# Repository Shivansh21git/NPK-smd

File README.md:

# 🌱 Bhoomitra (Krishi Sarthi) – Smart NPK Soil Monitoring System

## 📌 Overview

**Bhoomitra (Krishi Sarthi)** is an embedded + IoT-based smart agriculture system designed to monitor **soil nutrient levels (NPK)** and assist farmers in making data-driven fertilization decisions.

The latest version introduces a **compact, optimized hardware architecture**, making the system more portable, robust, and suitable for real-world deployment in farms.

---

## 🎯 Problem Statement

Farmers often apply fertilizers based on guesswork, which leads to:

* Overuse of chemicals
* Increased cost
* Soil degradation
* Reduced crop yield

**Bhoomitra solves this by providing real-time soil nutrient insights.**

---

## 🧠 System Architecture

### 🔷 High-Level Architecture

```
Soil → NPK Sensor → Microcontroller → Data Processing → Output (Display / IoT)
```

### 🔷 Functional Blocks

1. **Sensing Layer**

   * NPK sensor measures Nitrogen, Phosphorus, Potassium
2. **Processing Layer**

   * Microcontroller processes raw sensor data
3. **Communication Layer (optional)**

   * Sends data to cloud / mobile app (if IoT enabled)
4. **Output Layer**

   * Displays readings or recommendations

---

## 🔌 Hardware Architecture

### 🧩 Components Used

* NPK Soil Sensor
* Microcontroller (Arduino / ESP32 / similar)
* Power Supply Module
* Display (LCD/OLED) or Serial Output
* Communication Module (WiFi / GSM – optional)

### ⚙️ Hardware Design Improvements

* ✅ Compact PCB / module layout
* ✅ Reduced wiring complexity
* ✅ Lower power consumption
* ✅ Field-ready enclosure design
* ✅ Improved durability for outdoor usage

### 🔄 Data Flow (Hardware)

1. Sensor probes inserted into soil
2. Sensor outputs analog/digital signals
3. Microcontroller reads signals via ADC/UART
4. Data is processed and calibrated
5. Output is displayed or transmitted

---

## 💻 Software Architecture

### 🧱 Software Layers

#### 1. Sensor Interface Layer

* Handles communication with NPK sensor
* Reads raw values (via UART / Analog pins)

#### 2. Data Processing Layer

* Calibration of sensor values
* Conversion into usable NPK units
* Filtering noise (basic smoothing if applied)

#### 3. Logic Layer

* Determines soil fertility status
* Can map values to:

  * Low / Medium / High nutrient levels
* Optional: fertilizer recommendation logic

#### 4. Output Layer

* Serial Monitor / LCD display
* IoT dashboard (if connected)

---

## 🔄 Working Principle

1. The NPK sensor is inserted into soil.
2. It measures nutrient concentration levels.
3. Microcontroller reads and processes the data.
4. Values are converted into meaningful units.
5. Output is shown to the user or transmitted.
6. Farmer uses insights for fertilizer planning.

---

## 🌐 IoT Integration (Optional)

* Real-time monitoring via cloud
* Data logging for analysis
* Remote farm monitoring
* Mobile-based access

---

## 📊 Example Use Case

* Farmer checks soil before sowing
* Detects low nitrogen level
* Applies only required fertilizer
* Saves cost and improves yield

---

## 🚀 Advantages

* 🌱 Promotes precision agriculture
* 💰 Reduces fertilizer waste
* 📈 Improves crop productivity
* 📦 Compact and portable design
* 🔧 Easy to deploy and maintain

---

## 🔮 Future Enhancements

* AI-based fertilizer recommendation
* Mobile app integration
* GPS-based soil mapping
* Multi-parameter sensing (pH, moisture, temperature)

---

## 📂 Repository Contents

* Embedded code
* Circuit design / hardware files
* Documentation

---

## 👨‍💻 Author

Shivansh
**Project:** Bhoomitra (Krishi Sarthi)

---

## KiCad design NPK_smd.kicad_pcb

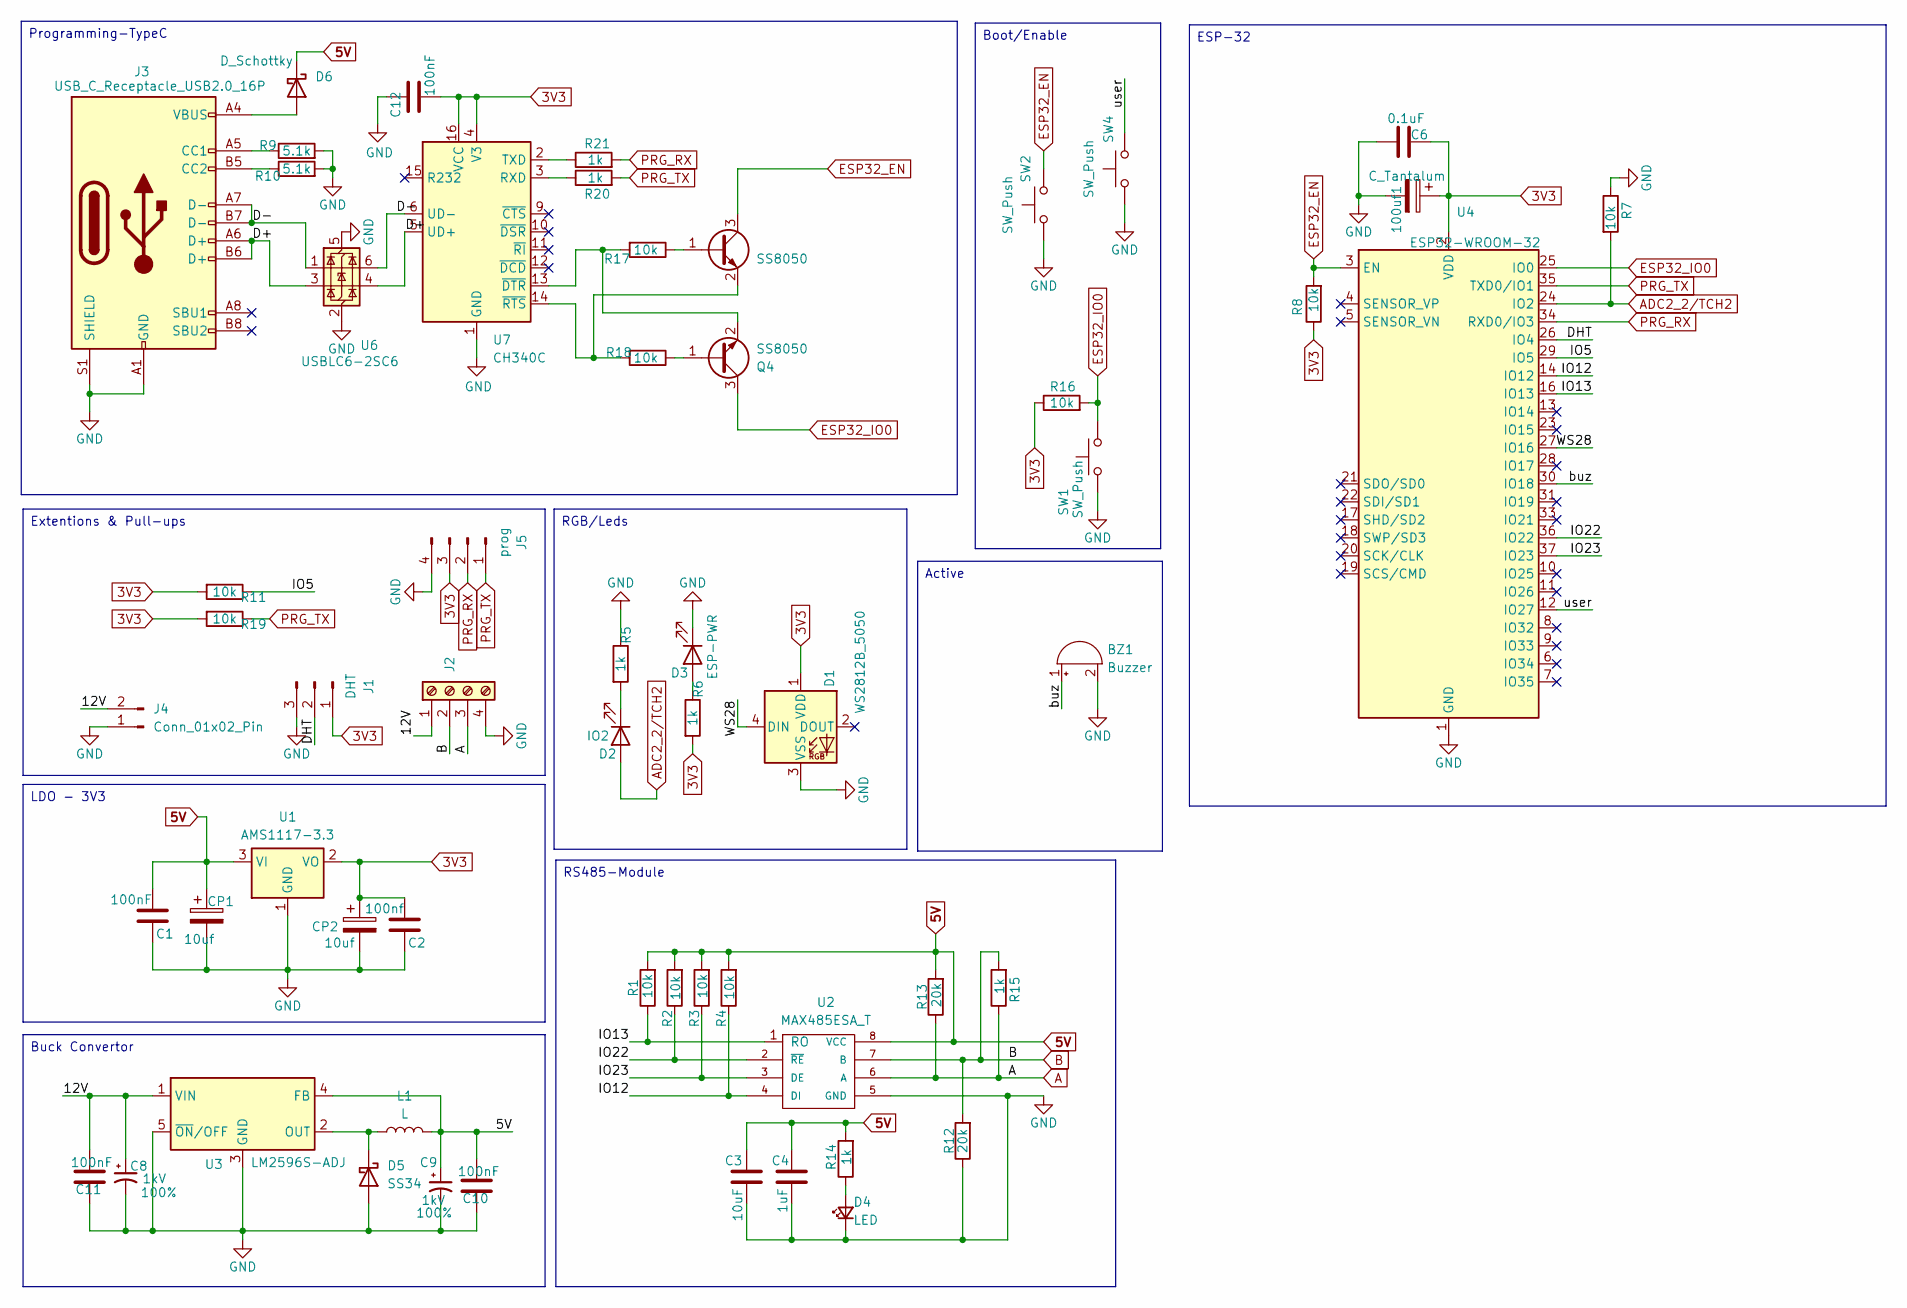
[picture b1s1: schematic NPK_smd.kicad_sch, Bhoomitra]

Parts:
100uf1: C_Tantalum; CP_EIA-3216-10_Kemet-I
BZ1: Buzzer; Buzzer_12x9.5RM7.6
C1, C10, C11, C12: 100nF; C_1206_3216Metric_Pad1.33x1.80mm_HandSolder
C2: 100nf; C_1206_3216Metric_Pad1.33x1.80mm_HandSolder
C3: 10uF; C_1206_3216Metric_Pad1.33x1.80mm_HandSolder
C4: 1uF; C_1206_3216Metric_Pad1.33x1.80mm_HandSolder
C6: 0.1uF; C_1206_3216Metric_Pad1.33x1.80mm_HandSolder
C8, C9: C_Polarized_Small; CP_Radial_D8.0mm_P3.50mm; Voltage 1kV; Tolerance 100%
CP1, CP2: 10uf; C_1206_3216Metric_Pad1.33x1.80mm_HandSolder
D1: WS2812B_5050; LED_WS2812B_PLCC4_5.0x5.0mm_P3.2mm
D2: IO2; C_1206_3216Metric_Pad1.33x1.80mm_HandSolder
D3: ESP-PWR; C_1206_3216Metric_Pad1.33x1.80mm_HandSolder
D4: LED; LED_1206_3216Metric
D5: SS34; D_SMA
D6: D_Schottky; R_0805_2012Metric_Pad1.20x1.40mm_HandSolder
J1: DHT; PinSocket_1x03_P2.54mm_Vertical
J2: Screw_Terminal_01x04; TerminalBlock_Xinya_XY308-2.54-4P_1x04_P2.54mm_Horizontal
J3: USB_C_Receptacle_USB2.0_16P; USB_C_Receptacle_GCT_USB4105-xx-A_16P_TopMnt_Horizontal
J4: Conn_01x02_Pin; solder-pad
J5: prog; PinHeader_1x04_P2.54mm_Vertical_SMD_Pin1Left
L1: L; L_10.4x10.4_H4.8
Q3, Q4: SS8050; SOT-23
R1, R2, R3, R4, R7, R8, R11, R16, R17, R18, R19: 10k; R_1206_3216Metric_Pad1.30x1.75mm_HandSolder
R5, R6, R14, R15, R20, R21: 1k; R_1206_3216Metric_Pad1.30x1.75mm_HandSolder
R9, R10: 5.1k; R_1206_3216Metric_Pad1.30x1.75mm_HandSolder
R12, R13: 20k; R_1206_3216Metric_Pad1.30x1.75mm_HandSolder
SW1, SW2, SW4: SW_Push; SW_B3U-1000PM
U1: AMS1117-3.3; SOT-223-3_TabPin2
U2: MAX485ESA_T; SOIC127P600X175-8N
U3: LM2596S-ADJ; TO-263-5_TabPin3
U4: ESP32-WROOM-32
U6: USBLC6-2SC6; SOT-23-6
U7: CH340C; SOIC-16_3.9x9.9mm_P1.27mm

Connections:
3V3: 100uf1.1, C2.2, C6.2, C12.2, CP2.1, D1.1 (VDD), J1.1, J5.3, R6.2, R8.1, R11.2, R16.1, R19.2, U1.2 (VO), U4.2 (VDD), U7.4 (V3), U7.16 (VCC)
5V: C1.2, C3.2, C4.2, C9.1, C10.2, CP1.1, D6.1 (K), L1.2, R1.2, R2.2, R3.2, R4.2, R13.2, R14.2, U1.3 (VI), U2.8 (VCC), U3.4 (FB)
/12V: C8.1, C11.2, J2.1, J4.2, U3.1 (VIN)
/D+: J3.A6 (D+), J3.B6 (D+), U6.3 (I/O2), U6.4 (I/O2), U7.5 (UD+)
/D-: J3.A7 (D-), J3.B7 (D-), U6.1 (I/O1), U6.6 (I/O1), U7.6 (UD-)
/DHT: J1.2, U4.26 (IO4)
/IO5: R11.1, U4.29 (IO5)
/IO12: R4.1, U2.4 (DI), U4.14 (IO12)
/IO13: R1.1, U2.1 (RO), U4.16 (IO13)
/IO22: R2.1, U2.2 (~RE), U4.36 (IO22)
/IO23: R3.1, U2.3 (DE), U4.37 (IO23)
/WS28: D1.4 (DIN), U4.27 (IO16)
/buz: BZ1.1 (+), U4.30 (IO18)
/user: SW4.2, U4.12 (IO27)
A: J2.3, R13.1, R15.1, U2.6 (A)
ADC2_2/TCH2: D2.2 (A), R7.2, U4.24 (IO2)
B: J2.2, R12.2, R15.2, U2.7 (B)
ESP32_EN: Q3.3 (C), R8.2, SW2.2, U4.3 (EN)
ESP32_IO0: Q4.3 (C), R16.2, SW1.2, U4.25 (IO0)
GND: 100uf1.2, BZ1.2 (-), C1.1, C2.1, C3.1, C4.1, C6.1, C8.2, C9.2, C10.1, C11.1, C12.1, CP1.2, CP2.2, D1.3 (VSS), D3.1 (K), D4.1 (K), D5.2 (A), J1.3, J2.4, J3.A1 (GND), J3.A12 (GND), J3.B1 (GND), J3.B12 (GND), J3.S1 (SHIELD), J4.1, J5.4, R5.1, R7.1, R9.2, R10.2, R12.1, SW1.1, SW2.1, SW4.1, U1.1 (GND), U2.5 (GND), U3.3 (GND), U3.5 (~ON/OFF), U4.1 (GND), U4.15 (GND), U4.38 (GND), U4.39 (GND), U6.2 (GND), U6.5 (VBUS), U7.1 (GND)
unnamed: D2.1 (K), R5.2
unnamed: D3.2 (A), R6.1
unnamed: D4.2 (A), R14.1
unnamed: D5.1 (K), L1.1, U3.2 (OUT)
unnamed: D6.2 (A), J3.A4 (VBUS), J3.A9 (VBUS), J3.B4 (VBUS), J3.B9 (VBUS)
unnamed: J3.A5 (CC1), R9.1
unnamed: J3.B5 (CC2), R10.1
unnamed: Q3.1 (B), R17.1
unnamed: Q3.2 (E), R18.2, U7.14 (~RTS)
unnamed: Q4.1 (B), R18.1
unnamed: Q4.2 (E), R17.2, U7.13 (~DTR)
unnamed: R20.1, U7.3 (RXD)
unnamed: R21.1, U7.2 (TXD)
PRG_RX: J5.2, R21.2, U4.34 (RXD0/IO3)
PRG_TX: J5.1, R19.1, R20.2, U4.35 (TXD0/IO1)

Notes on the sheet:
Boot/Enable
Buck Convertor
Extentions & Pull-ups
ESP-32
Active
RS485-Module
RGB/Leds
Programming-TypeC
LDO - 3V3

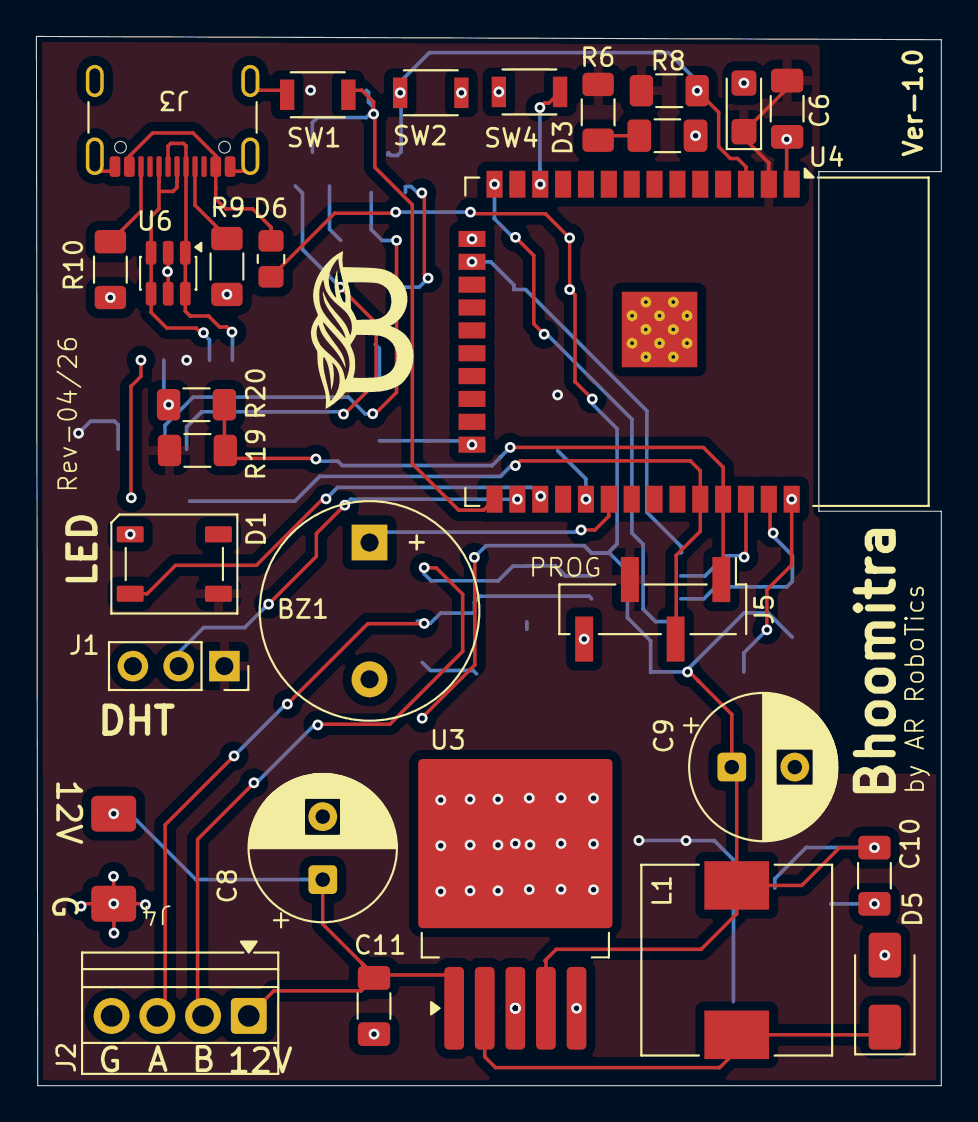
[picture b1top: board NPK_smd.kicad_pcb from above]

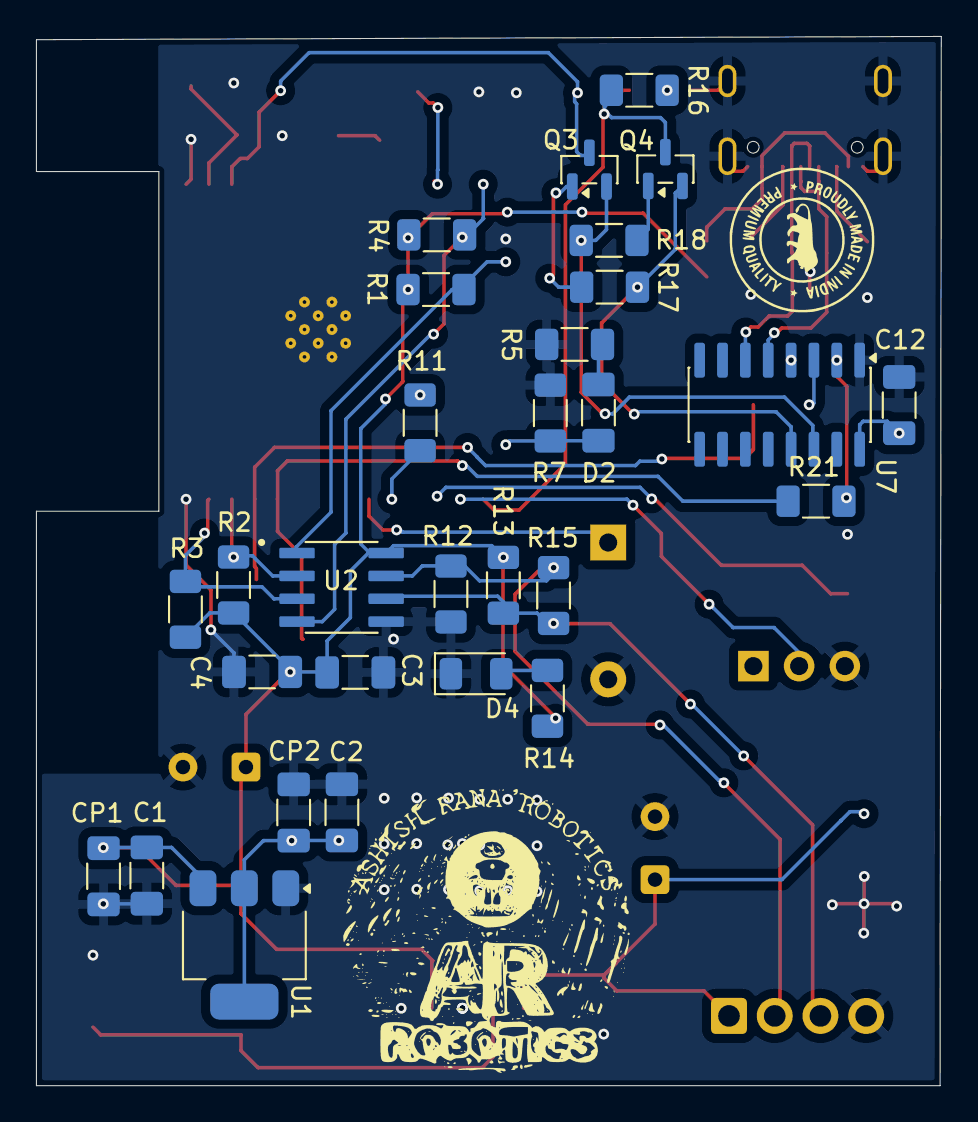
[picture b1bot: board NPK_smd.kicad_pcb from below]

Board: 2 copper layers, 50.3 x 58.3 mm, 58 parts (29 on the bottom side), 35 nets.

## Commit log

2026-03-13 NPK-smd version initial commit
2026-06-16 version-1.0 rev 2026-04-11
2026-06-16 size minimizations and updations
